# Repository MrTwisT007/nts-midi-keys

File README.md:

# What is this?
This is a project for a mini MIDI keyboard attachment for the Korg NTS-1 mini synthesizer I made circa 2021. It has two octaves of keys with octave switch buttons on either end. 

# What's in it?
This repo contains the KICAD files, arduino sketch to program the ATTiny45 and 3D stl files for the body attachment. I used an arduino mini to program the ATTiny as I did not have a suitable programmer at the time. Note, due to an error the footprint of the ATTiny is too narrow to fit the SOP package. Either edit the project file, or bend the pins of the MCU to fit it onto the board.

# Photos

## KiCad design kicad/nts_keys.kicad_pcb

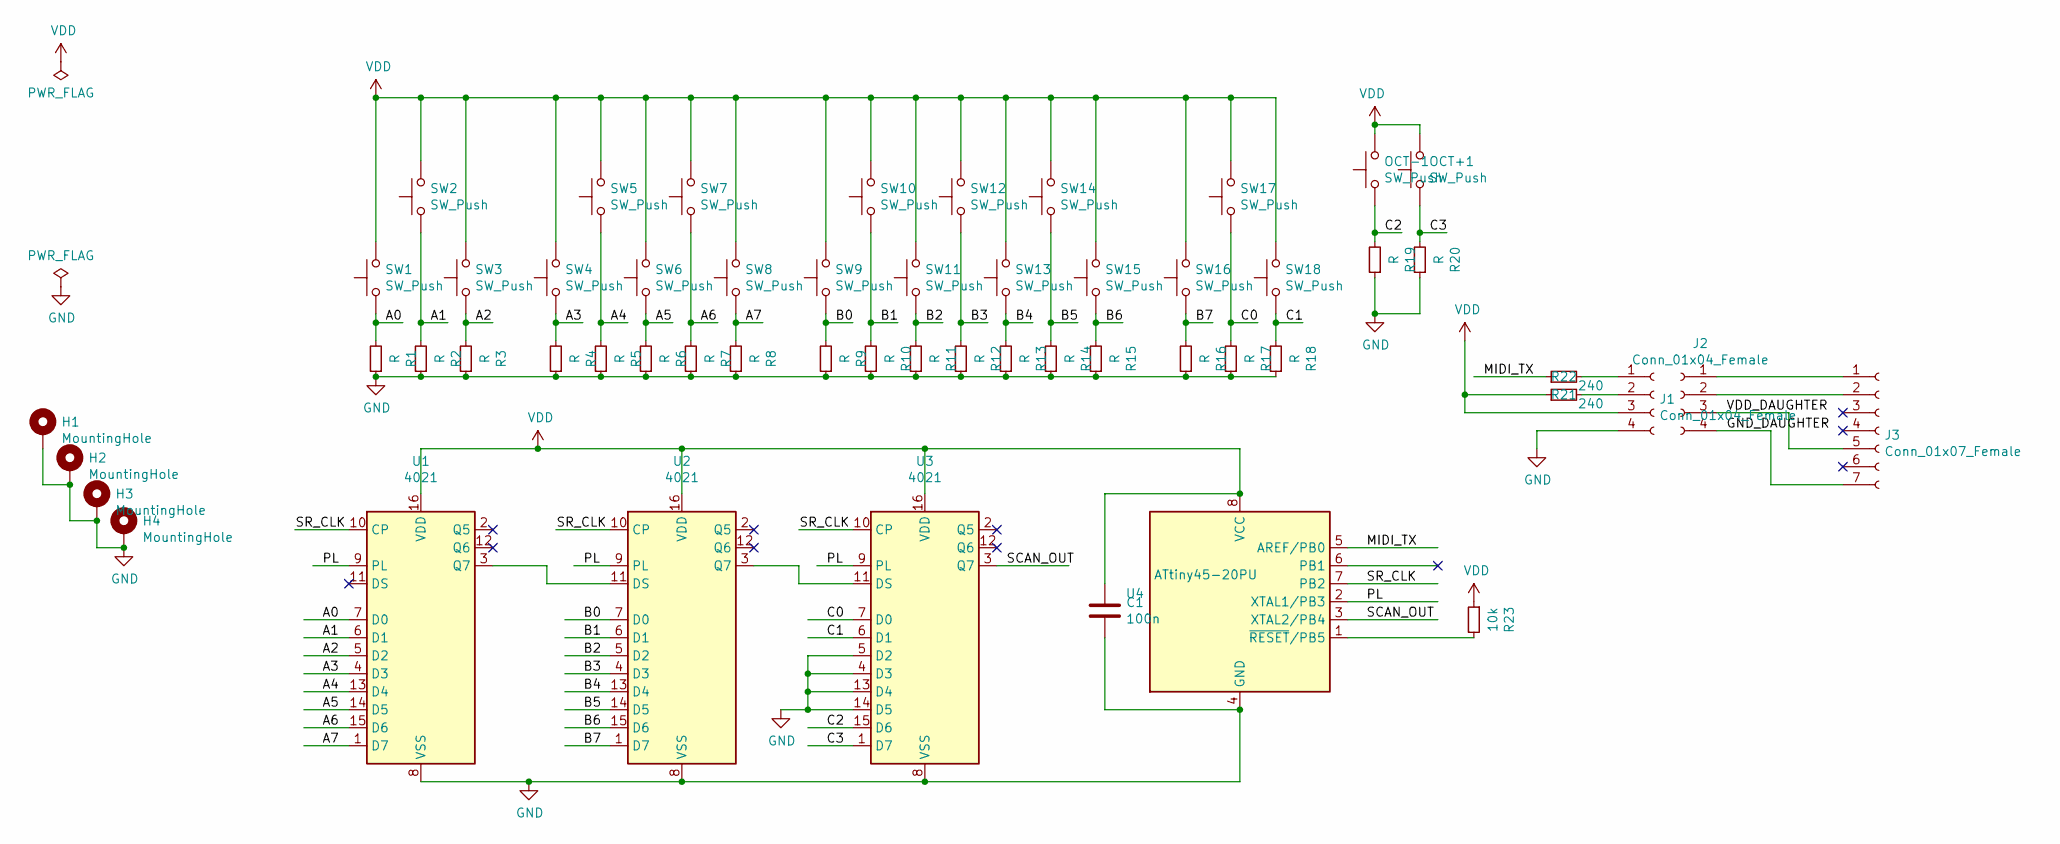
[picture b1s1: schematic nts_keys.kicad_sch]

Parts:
C1: 100n; C_1206_HandSoldering
H1, H2, H3, H4: MountingHole; MountingHole_3mm_Pad
J1, J2: Conn_01x04_Female; TE_84952-4_1x04_P1.0mm_Horizontal
J3: Conn_01x07_Female; Pin_Header_Straight_1x07_Pitch2.54mm
OCT+1: SW_Push; SW_SPST_EVQQ2
OCT-1: SW_Push; SW_SPST_EVQQ2
R1, R2, R3, R4, R5, R6, R7, R8, R9, R10, R11, R12, R13, R14, R15, R16, R17, R18, R19, R20: R; R_1206_HandSoldering
R21, R22: 240; R_1206_HandSoldering
R23: 10k; R_1206_HandSoldering
SW1, SW2, SW3, SW4, SW5, SW6, SW7, SW8, SW9, SW10, SW11, SW12, SW13, SW14, SW15, SW16, SW17, SW18: SW_Push; SW_SPST_EVQQ2
U1, U2, U3: 4021; SOIC-16_3.9x9.9mm_Pitch1.27mm
U4: ATtiny45-20PU; SOIJ-8_5.3x5.3mm_Pitch1.27mm

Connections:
/A0: R1.2, SW1.1, U1.7 (D0)
/A1: R2.2, SW2.1, U1.6 (D1)
/A2: R3.2, SW3.1, U1.5 (D2)
/A3: R4.2, SW4.1, U1.4 (D3)
/A4: R5.2, SW5.1, U1.13 (D4)
/A5: R6.2, SW6.1, U1.14 (D5)
/A6: R7.2, SW7.1, U1.15 (D6)
/A7: R8.2, SW8.1, U1.1 (D7)
/B0: R9.2, SW9.1, U2.7 (D0)
/B1: R10.2, SW10.1, U2.6 (D1)
/B2: R11.2, SW11.1, U2.5 (D2)
/B3: R12.2, SW12.1, U2.4 (D3)
/B4: R13.2, SW13.1, U2.13 (D4)
/B5: R14.2, SW14.1, U2.14 (D5)
/B6: R15.2, SW15.1, U2.15 (D6)
/B7: R16.2, SW16.1, U2.1 (D7)
/C0: R17.2, SW17.1, U3.7 (D0)
/C1: R18.2, SW18.1, U3.6 (D1)
/C2: OCT-1.1, R19.2, U3.15 (D6)
/C3: OCT+1.1, R20.2, U3.1 (D7)
/GND_DAUGHTER: J2.4, J3.7
/MIDI_TX: R22.1, U4.5 (AREF/PB0)
/PL: U1.9 (PL), U2.9 (PL), U3.9 (PL), U4.2 (XTAL1/PB3)
/SCAN_OUT: U3.3 (Q7), U4.3 (XTAL2/PB4)
/SR_CLK: U1.10 (CP), U2.10 (CP), U3.10 (CP), U4.7 (PB2)
/VDD_DAUGHTER: J2.3, J3.5
GND: C1.2, H1.1, H2.1, H3.1, H4.1, J1.4, R1.1, R2.1, R3.1, R4.1, R5.1, R6.1, R7.1, R8.1, R9.1, R10.1, R11.1, R12.1, R13.1, R14.1, R15.1, R16.1, R17.1, R18.1, R19.1, R20.1, U1.8 (VSS), U2.8 (VSS), U3.4 (D3), U3.5 (D2), U3.8 (VSS), U3.13 (D4), U3.14 (D5), U4.4 (GND)
unnamed: J1.1, R22.2
unnamed: J1.2, R21.2
unnamed: J2.1, J3.1
unnamed: J2.2, J3.2
unnamed: U1.3 (Q7), U2.11 (DS)
unnamed: U2.3 (Q7), U3.11 (DS)
unnamed: R23.2, U4.1 (~RESET/PB5)
VDD: C1.1, J1.3, OCT+1.2, OCT-1.2, R21.1, R23.1, SW1.2, SW2.2, SW3.2, SW4.2, SW5.2, SW6.2, SW7.2, SW8.2, SW9.2, SW10.2, SW11.2, SW12.2, SW13.2, SW14.2, SW15.2, SW16.2, SW17.2, SW18.2, U1.16 (VDD), U2.16 (VDD), U3.16 (VDD), U4.8 (VCC)

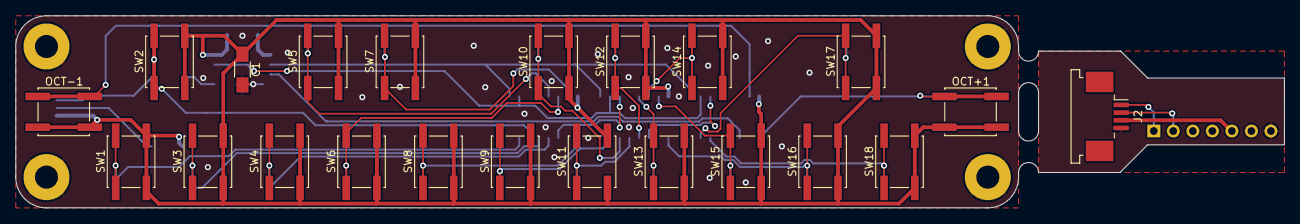
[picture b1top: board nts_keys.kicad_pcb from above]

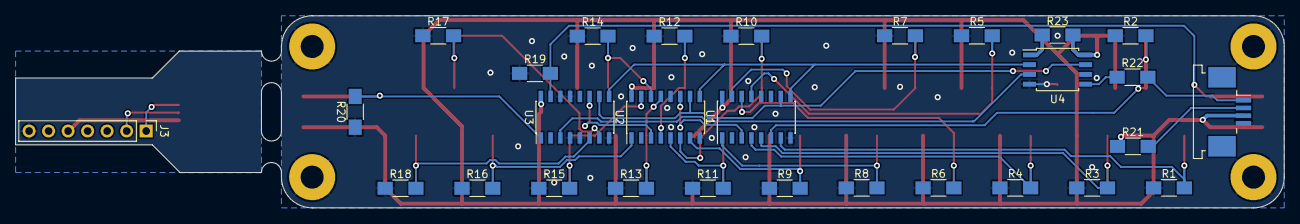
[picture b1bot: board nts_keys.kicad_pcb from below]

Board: 2 copper layers, 165.1 x 25.0 mm, 55 parts (29 on the bottom side), 35 nets.
